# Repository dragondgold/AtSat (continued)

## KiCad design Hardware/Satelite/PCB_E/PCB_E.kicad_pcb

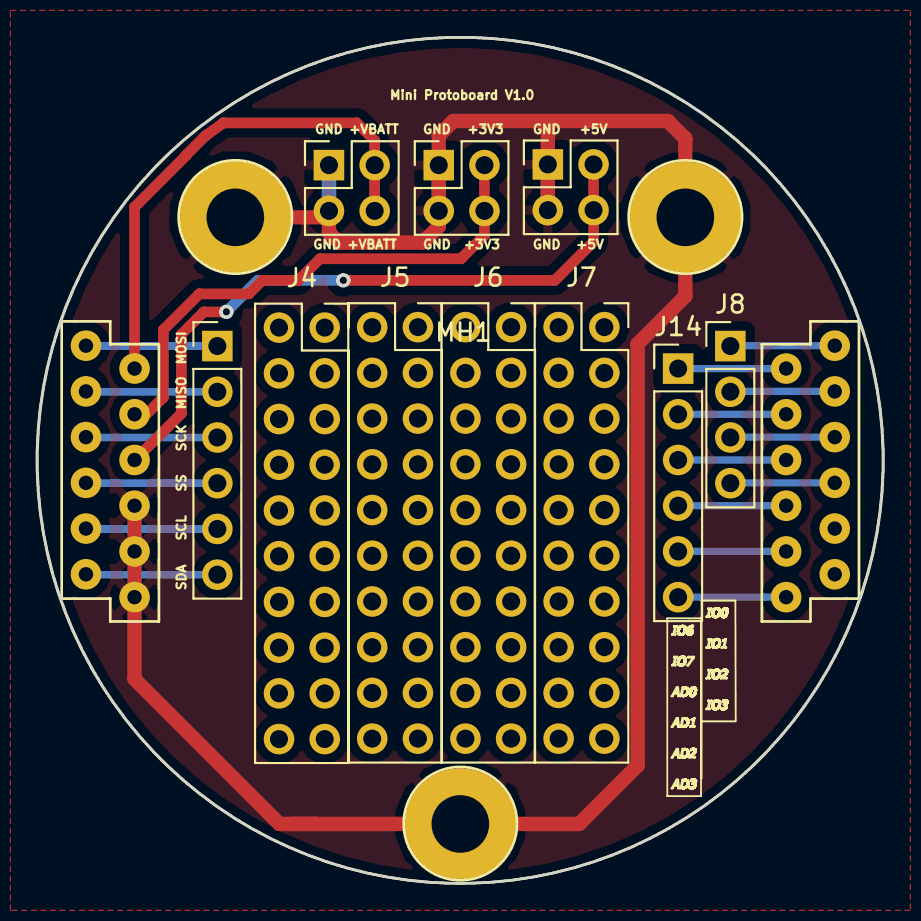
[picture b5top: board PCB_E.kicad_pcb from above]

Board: 2 copper layers, 47.0 x 47.0 mm, 15 parts (0 on the bottom side), 20 nets.

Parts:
J1, J2, J3: Conn_02x02_Counter_Clockwise; PinSocket_2x02_P2.54mm_Vertical
J4, J5, J6, J7: Conn_02x10_Odd_Even; PinSocket_2x10_P2.54mm_Vertical
J8: Conn_01x04; PinHeader_1x04_P2.54mm_Vertical
J12: Conector_Expansion_CanSat
J14, J15: Conn_01x06; PinHeader_1x06_P2.54mm_Vertical
M1, M2, M3: Spacer; Empty_Footprint
MH1: MH_CanSat

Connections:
+3V3: J3.3, J3.4, J12.14
+5V: J2.3, J2.4, J12.15
+BATT: J1.3, J1.4, J12.13
/AD0: J12.9, J14.3
/AD1: J12.10, J14.4
/AD2: J12.11, J14.5
/AD3: J12.12, J14.6
/IO0: J8.1, J12.1
/IO1: J8.2, J12.2
/IO2: J8.3, J12.3
/IO3: J8.4, J12.4
/IO6: J12.7, J14.1
/IO7: J12.8, J14.2
/MISO: J12.20, J15.2
/MOSI: J12.19, J15.1
/SCK: J12.21, J15.3
/SCL: J12.23, J15.5
/SDA: J12.24, J15.6
/SS: J12.22, J15.4
GND: J1.1, J1.2, J2.1, J2.2, J3.1, J3.2, J12.16, J12.17, J12.18, MH1.1, MH1.2, MH1.3

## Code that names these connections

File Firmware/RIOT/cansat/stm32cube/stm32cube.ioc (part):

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Mcu.Name=STM32F303R(D-E)Tx
Mcu.Package=LQFP64
Mcu.UserName=STM32F303RETx
PA0.Mode=IN1-Single-Ended
PA0.Signal=ADC1_IN1
PA1.Mode=IN2-Single-Ended
PA1.Signal=ADC1_IN2
PA10.Mode=I2C
PA10.Signal=I2C2_SDA
PA11.Mode=Device
PA11.Signal=USB_DM
PA12.Mode=Device
PA12.Signal=USB_DP
PA14.Signal=GPIO_Input
PA2.Signal=GPIO_Input
PA3.Mode=IN4-Single-Ended
PA3.Signal=ADC1_IN4
PA4.Mode=IN1-Single-Ended
PA4.Signal=ADC2_IN1
PA5.Mode=IN2-Single-Ended
PA5.Signal=ADC2_IN2
PA7.Signal=GPIO_Output
PA8.Mode=I2C
PA8.Signal=I2C3_SCL
PA9.Mode=I2C
PA9.Signal=I2C2_SCL
PB0.Signal=GPIO_Output
PB1.Signal=GPIO_Input
PB10.Signal=GPIO_Input
PB11.Signal=GPIO_Input
PB12.Signal=GPIO_Output
PB13.Mode=Full_Duplex_Master
PB13.Signal=SPI2_SCK
PB14.Mode=Full_Duplex_Master
PB14.Signal=SPI2_MISO
PB15.Mode=Full_Duplex_Master
PB15.Signal=SPI2_MOSI
PB2.Signal=GPIO_Input
PB3.Mode=Asynchronous
PB3.Signal=USART2_TX
PB4.GPIOParameters=GPIO_Speed,GPIO_PuPd
PB4.GPIO_PuPd=GPIO_PULLUP
PB4.GPIO_Speed=GPIO_SPEED_FREQ_MEDIUM
PB4.Mode=Asynchronous
PB4.Signal=USART2_RX
PB5.Signal=GPIO_Input
PB7.Signal=GPIO_Output
PB8.Signal=GPIO_Input
PB9.Signal=GPIO_Input
PC0.Signal=GPIO_Output
PC1.Signal=GPIO_Output
PC10.Mode=Full_Duplex_Master
PC10.Signal=SPI3_SCK
PC11.Mode=Full_Duplex_Master
PC11.Signal=SPI3_MISO
PC12.Mode=Full_Duplex_Master
PC12.Signal=SPI3_MOSI
PC13.Signal=GPIO_Output
PC14-OSC32_IN.Mode=LSE-External-Oscillator
PC14-OSC32_IN.Signal=RCC_OSC32_IN
PC15-OSC32_OUT.Mode=LSE-External-Oscillator
PC15-OSC32_OUT.Signal=RCC_OSC32_OUT
PC2.Signal=GPIO_Input
PC3.Signal=GPIO_Input
PC4.Signal=GPIO_Output
PC5.Signal=GPIO_Output
PC8.Signal=GPIO_Output
PC9.Mode=I2C
PC9.Signal=I2C3_SDA
PD2.Signal=GPIO_Input
PF0-OSC_IN.Mode=HSE-External-Oscillator
PF0-OSC_IN.Signal=RCC_OSC_IN
PF1-OSC_OUT.Mode=HSE-External-Oscillator
PF1-OSC_OUT.Signal=RCC_OSC_OUT
RCC.HSE_VALUE=8000000
RCC.SYSCLKFreq_VALUE=72000000
RCC.SYSCLKSourceVirtual=RCC_SYSCLKSOURCE_PLLCLK
board=custom

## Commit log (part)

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2018-10-29 Conector PCB B-C lado B modificado
2018-10-31 Cambios en algunos pines del conector B-C
2018-11-02 Pequeñas mejoras en PCB_C
2018-11-04 Modifificaciones de pines en conector PCB_B-C
2018-11-04 PCB C actualizado con nuevo conector (WIP)
2018-11-05 PCB_B Terminado sujeto a revision
2018-11-05 Modificado PCB C para la nueva dispocisión del conector B-C
2018-11-06 Correciones de anchos de trazas en PCB A
2018-11-06 Correciones en PCB D
2018-11-06 Numeros de parte para PCB_A. Se movió también el switch de encendido más afuera para fácil acceso.
2018-11-06 Numeros de parte para PCB_B
2018-11-07 Numeros de parte para PCB_E
2018-11-07 Modificaciones en PCB_E y nuevas serigrafias
2018-11-07 Agregado boton de reset para Arduino en PCB_D
2018-11-07 Espaciador de 10mm para PCB_A
2018-11-08 Modelos 3D de PCB (WIP)
2018-11-08 Indicador de conectores de servo en PCB_A
2018-11-08 Modificado conector A-B para poder alojar la batería entre A y B
2018-11-08 Movidos componentes de bot a top en PCB D
2018-11-08 Agregado TPD2E2U06 a PCB D
2018-11-08 Agregado pull-down para pin BOOT0
2018-11-08 Agregados logos en PCB_B
2018-11-08 Agregados logos en PCB_D y headers con tx y rx para debug
2018-11-12 RIOT OS 2018.07
2018-11-12 Proyecto base del firmware de CanSat con instrucciones para configurar el ambiente de desarrollo
2018-11-13 Agregado vuetify desde vue cli
2018-11-14 Agregado librerias de stm32cube
2018-11-17 Más codigo de inicialización para el CanSat
2018-11-19 Agregado manager para las fuentes auxiliares de 3.3V y 5V
2018-11-22 Driver para ADC
2018-11-27 Plugin para generación de BOM en KiCad
2018-11-27 BOM PCB_B y corrección a numeros de parte
2018-11-27 Corrección de numero de partes en PCB_A
2018-11-27 BOM y corrección de numero de partes en PCB_E
2018-11-29 Agregados agujeros para pasar cable de bateria a top en PCB_A
2018-11-30 Componentes 0402 para el CC1101 en estación terrena
2018-12-03 BOM estación terrena
2018-12-17 Uso de Vuex, añadida primer funcion de crear y cargar proyecto + utils
2018-12-26 Cambios iniciales en el esquema de PCB_C para utilizar el EPS32 en lugar del STM32F303RE
2018-12-26 Agregado de BJT para encender el LED controlado por el supervisor
2018-12-27 PCB_C con ESP32
2018-12-28 Cambios en PCB_C para el nuevo conextor de expansión que lleva VBus ahora
2018-12-28 Pequeñas mejoras en PCB_B
2018-12-28 Agregado a estación terrena el capacitor de bloqueo para el balun 885012005046
2018-12-28 Modificaciones en serigrafia conector expansion
2018-12-28 Modificaciones D6 y serigrafia en PCB_E
2018-12-28 Serigrafias en leds PCB_A
2018-12-28 Agregado fusible para batería en PCB_A
2018-12-28 Primer modelo 3D para ESP32-WROOM-32
2018-12-28 Modelos 3D para PCB_C
2018-12-29 Arreglos serigrafía PCB_E
2018-12-29 Paths relativos para modelos 3D del PCB_C
2018-12-29 Corregido MISO y MOSI al revés
2018-12-31 Agregados pines faltantes en PCB_E
2019-01-02 Modelos 3D faltantes en PCB_C
2019-01-02 Corrección modelo 3D en PCB_C
2019-01-02 Logo open hardware en esquemáticos
2019-01-02 Agregados testpoint a Estacion terrena y modificado jumper de CS
2019-01-02 Actualización BOM
2019-01-02 Actualizado BOM estacion terrena
2019-01-03 Agregados testpoint a PCB_C
2019-01-03 Más mejoras en el plano de masa de PCB_C
2019-01-03 Corrección de DRC en PCB_C
2019-01-04 Añadidos modelos 3D en PCB_A
2019-01-04 WIP modelos 3D a PCB_D (Revisar U3)
2019-01-04 Eliminado modelo 3D no usado
2019-01-05 PCB de antena para el satélite
2019-01-06 Create LICENSE
2019-01-09 Silkscreen para PCB antena
2019-01-09 Archivos gerber para los PCB
2019-01-09 Agregados logos en PCB ET
2019-01-10 Pequeño arreglo para prevenir redirección al soltar un archivo en la app
2019-01-11 Agregados modelos 3D faltantes a PCB_B
2019-01-12 Modelo 3D para MS563702BA03
2019-01-16 Agregados iconos a home
2019-01-17 Agregados cortes para switch y USB del satélite
2019-01-19 Materiales con densidad correspondiente para los modelos 3D
2019-01-19 Añadida información faltante en rótulos de los esquemas
2019-01-19 Símbolo de esquema faltante
2019-01-21 Arreglo en sistema de notificaciones
2019-01-21 Submodulo esp-idf
2019-01-21 Código inicial del firmware. Managers principales para los sistemas del satélite.
2019-01-22 Más managers, mejor manejo de errores, más codigo, un poco de todo XD
2019-01-25 Usar newlib nano para reducir el stack utilizado por funciones como printf y ESP_LOGx. Habilitadas funciones estáticas de FreeRTOS.
2019-01-25 Driver para sensor de humedad Si7006
2019-01-25 Modificados componentes del asistente de proyecto
2019-01-26 Driver para IMU (WIP)
2019-01-26 Métodos para obtener humedad
2019-01-27 Agregado sensor_manager para la administración de todos los sensores (WIP) y librería de NXP de sensor fusion para obtener la orientación a través del IMU.
2019-01-27 Pequeña limpieza de código en sensor fusion
2019-01-28 Driver para fuel gauge BQ27441
2019-01-29 Corrección de error en i2c_manager no enviando la dirección del registro a modificar
2019-01-29 Sensor fusion de 9 DOF (aun hay problemas con el drift)
2019-01-29 Agregado battery_manager
2019-01-29 Eliminado warning del compilador
2019-01-29 Movida la librería minmea a libs/
2019-01-30 Agregado administrador de servos servo_manager
2019-01-30 Agregado led_manager para control del LED
2019-01-31 Corrección de errores por NULL pointer esporádicos en sensor_manager
2019-01-31 Incrementado el tamaño del stack de las tareas
2019-01-31 Actuadores, sensores, fuentes y GPS Ui terminado (Revisar en producción)
2019-01-31 Configuración del módulo SPI en spi_manager
2019-02-01 Driver para CC1101
2019-02-01 Tests UI y notificaciones asociadas terminadas(falta def código notific)
2019-02-02 Improved delays in cc1101 driver
2019-02-04 Corregido mala disposición de los diodos D5 y D6 en PCB_D
2019-02-04 Mejor logging de errores en sensor de presión y humedad
2019-02-04 Más logging en battery_manager
2019-02-05 Reducción del clock del bus I2C interno a 20 kHz para correcto funcionamiento con fuel-gauge
2019-02-05 Comprobaciones adicionales para driver de BQ27441
2019-02-05 Incrementado tamaño del stack de battery_manager
2019-02-05 Alertas al conectar/desconectar el cargador
2019-02-05 Corrección de bugs y comprobaciones adicionales en driver de CC1101
2019-02-05 Agregado código para enviar datos con CC1101
2019-02-06 Corrección de valores de duty para los servos
2019-02-06 Línea comentada por accidente
2019-02-06 Pequeño arreglo en mision
2019-02-06 Comprobaciones adicionales para paquetes recibidos en el driver de CC1101
2019-02-07 Máxima capacidad de corriente para los pines SPI
2019-02-07 Code snippet
2019-02-07 Mecanismo de reintentos para inicialización del sensor de presión
2019-02-07 Reducción del tiempo en que battery_manager toma el mutex
2019-02-07 Código para transmición de datos a estación terrena
2019-02-07 Terminado Gráficos en misiones
2019-02-08 Código faltante para el PIC16
2019-02-08 Pequeño bug en carga de misiones arreglado
2019-02-08 Corrección de errores de compilación
2019-02-09 Corrección de múltiples errores en PIC16 y recepción de datos en el ESP32
2019-02-09 Agregado envío de datos de los comandos de corrientes y tensiones
2019-02-09 Incrementada la frecuencia de la tarea sensor fusion
2019-02-10 Primer commit de driver de CC1101 en javascript
2019-02-10 Code to use the MCP2210CLI.exe in the CC1101 javascript driver
2019-02-11 Arreglo de funciones en driver CC1101 de javascript
2019-02-12 Corrección de varios errores en el driver de CC1101 de javascript
2019-02-12 Mejoras del driver CC1101 y código para testing de comunicación
2019-02-12 Corrección de errores en recepción y decodificación de paquetes
2019-02-13 Agregado sensor orientación
2019-02-13 Correccion de algunos bugs e integración del nuevo CLI
2019-02-13 Código de ejemplo de worker.js
2019-02-14 Agregado nuevo CLI a electron-builder.yml
2019-02-14 Preservar bit de signo en el envío de coordenadas GPS
2019-02-14 Mejoras en los brazos de los servos y base del paracaídas
2019-02-14 Agregado README explicando requerimientos para mcp2210-cli
2019-02-14 Agregado logs a com_manager
2019-02-14 Corrección en envío de valores con signo
2019-02-15 Código inicial para reporte automático de datos y movido GPS como tipo de sensor
2019-02-15 Parpadeo de LED al recibir datos
2019-02-15 Nuevos ID para sensores
2019-02-15 Soporte experimental para manejo de GPIO desde mcp2210-cli
2019-02-15 Interpretación de multiples ids en comando getSensor
2019-02-15 RSSI puede ser negativo o positivo
2019-02-16 Agregado comando 0x09
2019-02-16 Código inicial para parser de comandos desde el Arduino
2019-02-16 Cambios en los IDs de sensores
2019-02-17 Agregada logica para ocultar sensores y pequeños arreglos
2019-02-18 Agregado cmd 0x09 habilitar fuentes
2019-02-18 Carga de muestras, errores y actuadores + arreglos en modelo et
2019-02-18 Nuevos valores de registros para CC1101 en estación terrena y agregado cálculo de RSSI en dbm
2019-02-18 Corrección de error en com_manager cuando el mutex no podía ser tomado se accedía al CC1101 de todas formas. También se cambió el método de envío automático intercalando entre sensores y datos de cor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
2019-02-19 Arreglo de unidades y gráficos
2019-02-19 Excel de TI para cálculo de distancias de enlaces RF
2019-02-20 Agregado comprobación de baja tensión para detección de cortocircuitos en el satélite
2019-02-20 Arreglos en la UI
2019-02-20 Validación de longitud de muestras en misiones comentada
2019-02-20 Más codigo para el API del supervisor
2019-02-20 Agregado byte de validación de gps
2019-02-20 Arreglado bug de nombre de cansat en mision
2019-02-20 Worker modificado la app pide siempre a cansat excepto los errores
2019-02-21 Más mejoras al modelo mecánico
2019-02-21 Cambios de logos en esquemas
2019-02-21 Alojamientos para tuercas M3 en cuerpo Sat
2019-02-21 Soporte para antena
2019-02-22 Código inicial para PIC18 conversor USB-SPI
2019-02-22 Decodificador de protocolo para conversor USB-SPI
2019-02-22 Agregado checksum y tipo de dato al protocolo del conversor USB-SPI
2019-02-22 Mejora del protocolo y agregada funcionalidad SPI en el conversor USB-SPI
2019-02-23 Nuevo workerTest.js
2019-02-23 Agregado comando de consola para habilitar fuentes
2019-02-23 Enviar estado de los servos al cerrarlos automáticamente
2019-02-24 Modificado período de reporte automático por defecto
2019-02-24 Establecer conexion serial port UI y worker
2019-02-25 Test y conexión con CanSat
2019-02-25 Parser de comandos provenientes del conector de expansión
2019-02-25 Corrección paquete CANSAT_ENABLE_DISABLE_PS no respondía de manera correcta
2019-02-25 Arreglos en la activación de fuentes
2019-02-25 Agregado comando 0x0C
2019-02-25 Pequeños arreglos en UI y en creación de proyecto
2019-02-26 Indicar con LED cuando el satélite está cargando su batería
2019-02-26 Piso paracaidaSat modificado
2019-02-27 Agregada bateria y señal en navbar
2019-02-27 Mejoras en piezas mecánicas y agregado de tornillos
2019-03-03 Varios cambios estructurales y visuales a la estructura
2019-04-08 Pequeños arreglos en UI + pruebas con vue-highchart
2019-04-29 Agregado paths de librerías de KiCad necesarias en PCB_A
2020-02-29 Initial working v2 firmware for CanSat. A basic firmware running FreeRTOS and BLE as a peripheral (I may need to change it to central instead, makes more sense).
2020-03-07 Added aux_ps_manager (not working with power_monitor yet)
2020-12-13 Bump ini from 1.3.5 to 1.3.8 in /desktop-app
    Bumps [ini](https://github.com/isaacs/ini) from 1.3.5 to 1.3.8.
    - [Release notes](https://github.com/isaacs/ini/releases)
    - [Commits](https://github.com/isaacs/ini/compare/v1.3.5...v1.3.8)
